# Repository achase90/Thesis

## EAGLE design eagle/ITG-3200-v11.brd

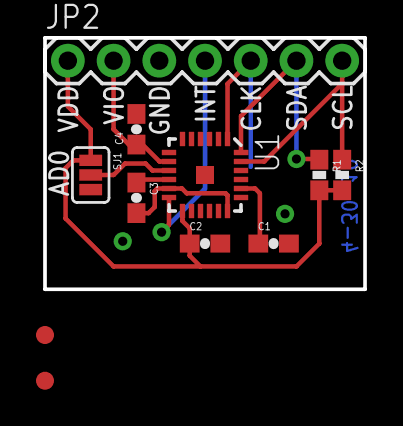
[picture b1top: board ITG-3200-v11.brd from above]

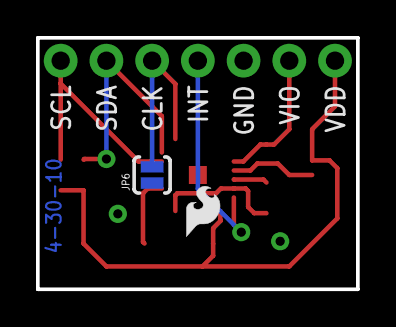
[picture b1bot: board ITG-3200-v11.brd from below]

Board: 2 copper layers, 17.8 x 14.0 mm, 13 parts (2 on the bottom side), 10 nets.

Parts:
C1: 2.2nF; 0603-CAP
C2, C3: 0.1uF; 0603-CAP
C4: 10nF; 0603-CAP
JP1: LOGO-SFESK; SFE-LOGO-FLAME
JP2: 1X07
JP3, JP4: FIDUCIAL1X2; FIDUCIAL-1X2
JP6: SJ_2S-NO
R1, R2: DNP; 0603-RES
SJ1: SJ_3_PASTE1&2
U1: ITG-3200; QFN-24

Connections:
ADO: SJ1.2, U1.9
CLKIN: JP2.5, JP6.2, U1.1
GND: C1.2, C2.2, C3.2, C4.2, JP2.3, JP6.1, SJ1.3, U1.11, U1.18
INT: JP2.4, U1.12
unnamed: C1.1, U1.20
unnamed: C3.1, U1.10
SCL: JP2.7, R2.1, U1.23
SDA: JP2.6, R1.1, U1.24
VCC: C2.1, JP2.1, R1.2, R2.2, SJ1.1, U1.13
VLOGIC: C4.1, JP2.2, U1.8
